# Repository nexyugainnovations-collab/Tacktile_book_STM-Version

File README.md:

# Tacktile Book STM (v1.0)

STM32-based hardware design for the Tacktile book, an interactive tactile book that plays audio in response to touch. This repository contains the PCB design files and the audio content used by the device.

Developed by **Nexyuga Innovations**.

## Contents

| Folder | Description |
|--------|-------------|
| pcb/ | Schematic and board layout source files |
| gerber/ | Fabrication outputs (Gerbers, drill files) |
| bom/ | Bill of materials |
| audio/ | Audio files used by the device |
| docs/ | Datasheets, notes and images |

Folder names may differ slightly from the actual layout. Update the table to match the repository.

## Hardware

- **Microcontroller:** STM32 (part number: TBD)
- **PCB design tool:** TBD
- **Audio:** stored audio played back through an amplifier and speaker
- **Input:** touch or button input from the tactile pages

## Getting Started

Clone the repository:

    git clone https://github.com/nexyugainnovations-collab/Tacktile_book_STM-Version.git
    cd Tacktile_book_STM-Version

1. Open the project file from the pcb/ folder in your PCB design tool.
2. To manufacture the board, send the contents of gerber/ to a PCB fabricator and use bom/ for component sourcing.
3. Flash the firmware to the STM32 using STM32CubeProgrammer or an ST-Link.

## Version History

| Version | Notes |
|---------|-------|
| v1.0 | Initial release: PCB and audio files |

## Contributors

- Pravin Balu ([*****](https://github.com/*****))
- Nithilan Saravanan ([@nithilan0710](https://github.com/nithilan0710))
- Nexyuga Innovations

## License

Proprietary. All rights reserved by Nexyuga Innovations.

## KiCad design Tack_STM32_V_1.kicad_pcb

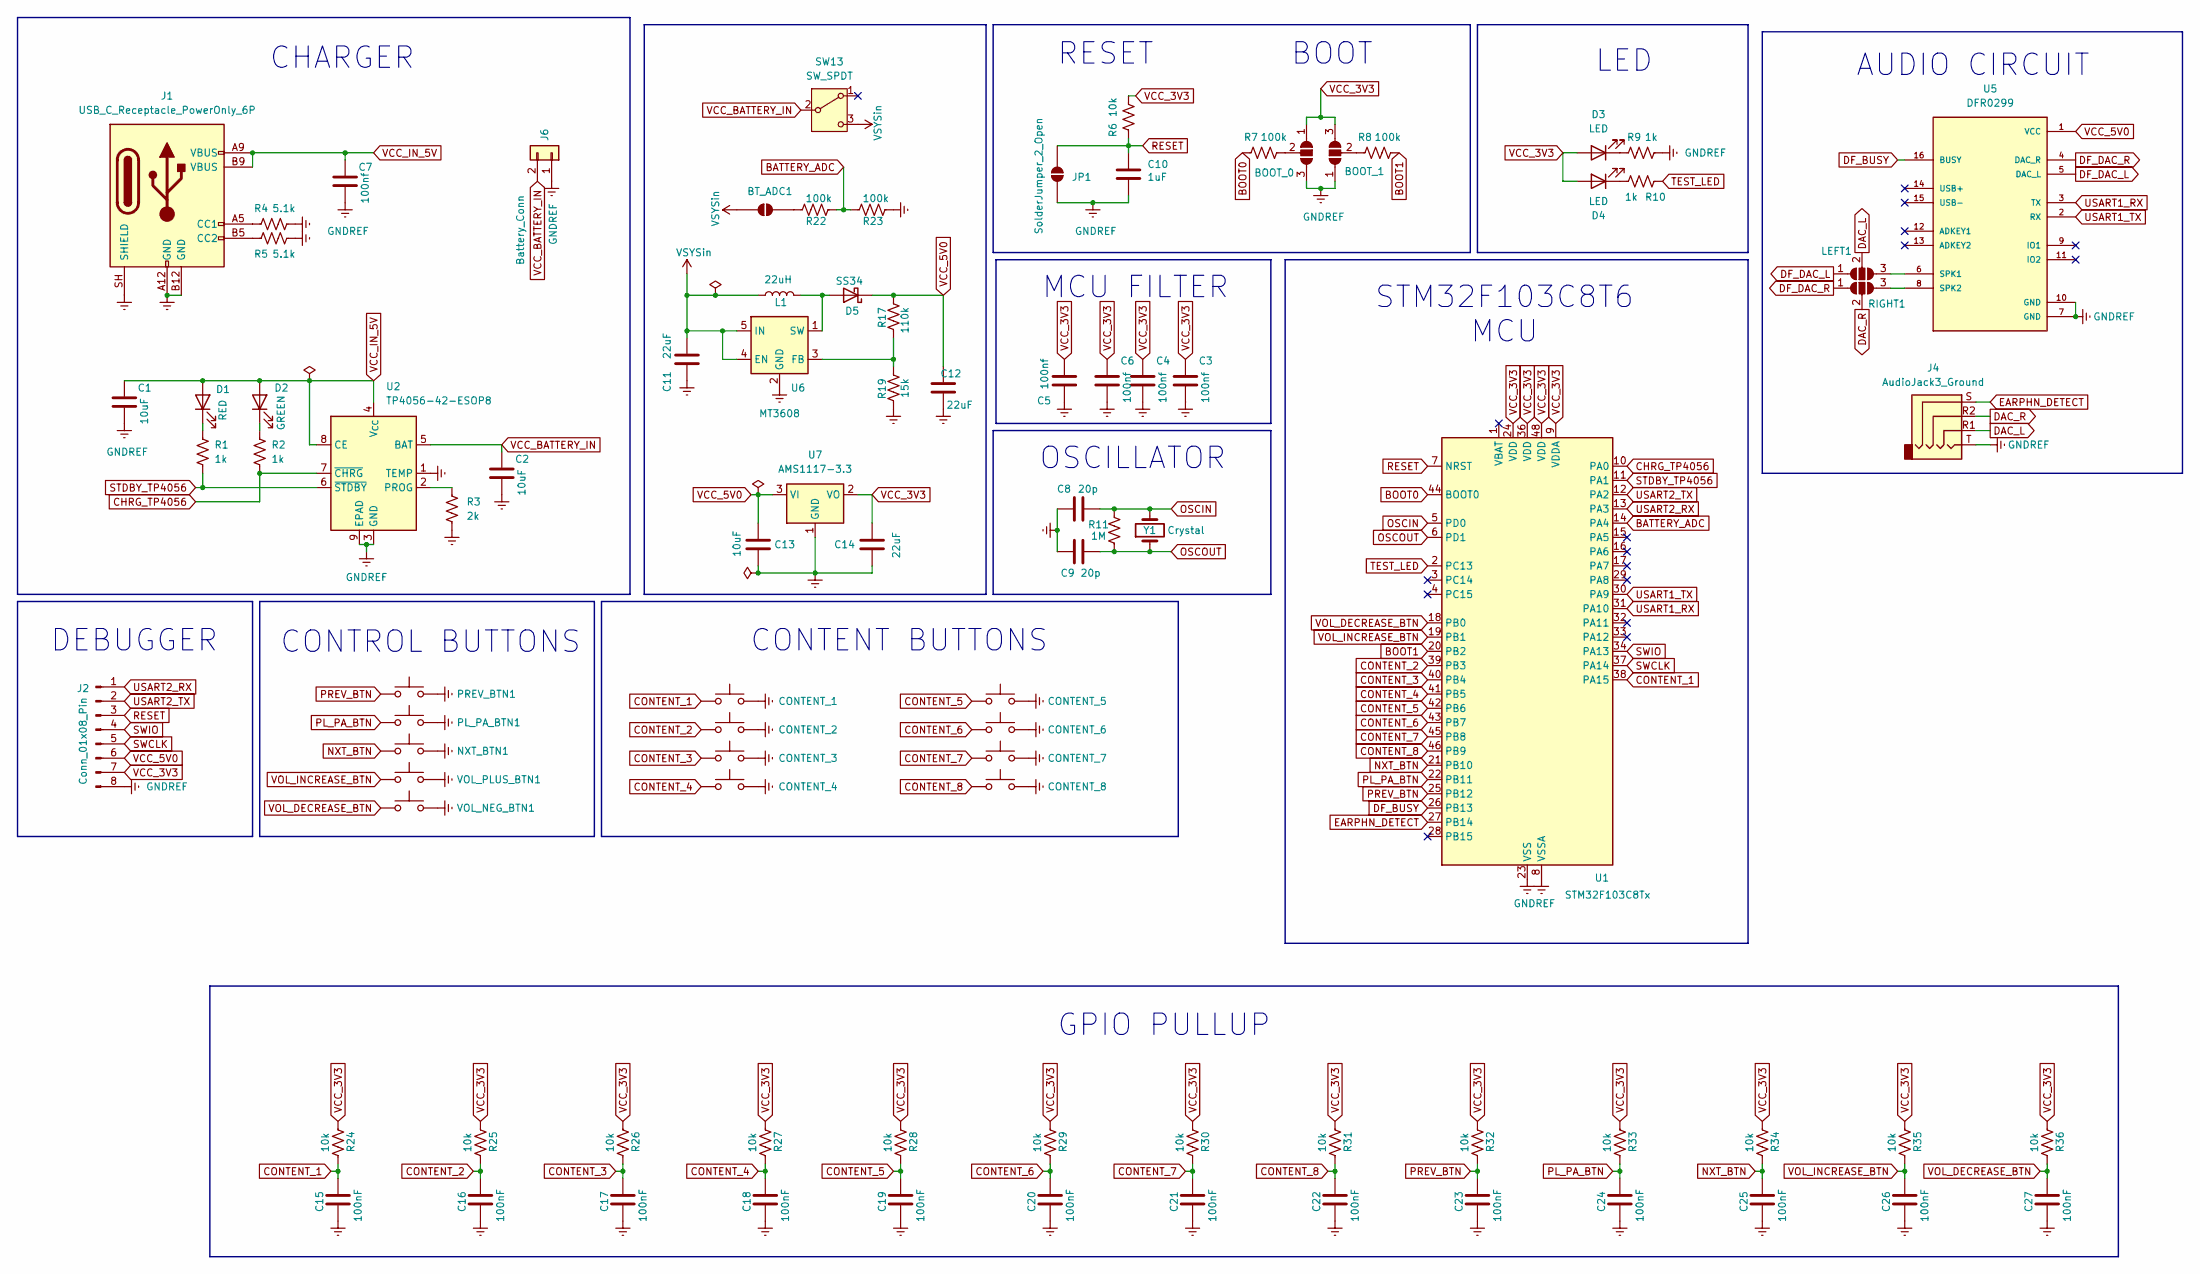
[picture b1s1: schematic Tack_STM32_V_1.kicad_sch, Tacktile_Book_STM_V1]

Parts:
BOOT_0, BOOT_1: SolderJumper_3_Open; SolderJumper-3_P1.3mm_Open_Pad1.0x1.5mm
BT_ADC1: SolderJumper_2_Open; SolderJumper-2_P1.3mm_Open_RoundedPad1.0x1.5mm
C1, C2, C13: 10uF; C_0603_1608Metric_Pad1.08x0.95mm_HandSolder
C3, C4, C5, C6, C7: 100nf; C_0603_1608Metric_Pad1.08x0.95mm_HandSolder
C8, C9: 20p; C_0603_1608Metric_Pad1.08x0.95mm_HandSolder
C10: 1uF; C_0603_1608Metric_Pad1.08x0.95mm_HandSolder
C11, C12, C14: 22uF; C_0603_1608Metric_Pad1.08x0.95mm_HandSolder
C15, C16, C17, C18, C19, C20, C21, C22, C23, C24, C25, C26, C27: 100nF; C_0603_1608Metric_Pad1.08x0.95mm_HandSolder
CONTENT_1: CONTENT_1; SW_CONTENT_2.5mm
CONTENT_2: CONTENT_2; SW_CONTENT_2.5mm
CONTENT_3: CONTENT_3; SW_CONTENT_2.5mm
CONTENT_4: CONTENT_4; SW_CONTENT_2.5mm
CONTENT_5: CONTENT_5; SW_CONTENT_2.5mm
CONTENT_6: CONTENT_6; SW_CONTENT_2.5mm
CONTENT_7: CONTENT_7; SW_CONTENT_2.5mm
CONTENT_8: CONTENT_8; SW_CONTENT_2.5mm
D1: RED; LED_0805_2012Metric_Pad1.15x1.40mm_HandSolder
D2: GREEN; LED_0805_2012Metric_Pad1.15x1.40mm_HandSolder
D3, D4: LED; LED_0805_2012Metric_Pad1.15x1.40mm_HandSolder
D5: SS34; D_SMB
J1: USB_C_Receptacle_PowerOnly_6P; USB_C_Receptacle_HRO_TYPE-C-31-M-17
J2: Conn_01x08_Pin; JST_PH_B8B-PH-K_1x08_P2.00mm_Vertical
J4: AudioJack3_Ground; Jack_3.5mm_PJ320D_Horizontal
J6: Battery_Conn; JST_EH_S2B-EH_1x02_P2.50mm_Horizontal
JP1: SolderJumper_2_Open; SolderJumper-2_P1.3mm_Open_RoundedPad1.0x1.5mm
L1: 22uH; L_Inductor 22uH – 5.2×5.8×4.5mm – CD54 – SMD
LEFT1: SolderJumper_3_Open; SolderJumper-3_P1.3mm_Open_Pad1.0x1.5mm
NXT_BTN1: NXT_BTN; SW_Tactile_SPST_Angled_PTS645Vx58-2LFS
PL_PA_BTN1: PL_PA_BTN; SW_Tactile_SPST_Angled_PTS645Vx58-2LFS
PREV_BTN1: SW_Tactile_SPST_Angled_PTS645Vx58-2LFS
R1, R2, R9, R10: 1k; R_0603_1608Metric_Pad0.98x0.95mm_HandSolder
R3: 2k; R_0603_1608Metric_Pad0.98x0.95mm_HandSolder
R4, R5: 5.1k; R_0603_1608Metric_Pad0.98x0.95mm_HandSolder
R6, R24, R25, R26, R27, R28, R29, R30, R31, R32, R33, R34, R35, R36: 10k; R_0402_1005Metric_Pad0.72x0.64mm_HandSolder
R7, R8, R22, R23: 100k; R_0603_1608Metric_Pad0.98x0.95mm_HandSolder
R11: 1M; R_0603_1608Metric_Pad0.98x0.95mm_HandSolder
R17: 110k; R_0603_1608Metric_Pad0.98x0.95mm_HandSolder
R19: 15k; R_0402_1005Metric_Pad0.72x0.64mm_HandSolder
RIGHT1: SolderJumper_3_Open; SolderJumper-3_P1.3mm_Open_Pad1.0x1.5mm
SW13: SW_SPDT; SS12F23G5 Mini SPDT Slide Switch Right Angle
U1: STM32F103C8Tx; LQFP-48_7x7mm_P0.5mm
U2: TP4056-42-ESOP8; SOIC-8-1EP_3.9x4.9mm_P1.27mm_EP2.41x3.3mm_ThermalVias
U5: DFR0299; MODULE_DFR0299
U6: MT3608; SOT-23-6
U7: AMS1117-3.3; SOT-223-3_TabPin2
VOL_NEG_BTN1: VOL_NEG_BTN; SW_Tactile_SPST_Angled_PTS645Vx58-2LFS
VOL_PLUS_BTN1: VOL_PLUS_BTN; SW_Tactile_SPST_Angled_PTS645Vx58-2LFS
Y1: Crystal; Crystal_SMD_HC49-SD

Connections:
BATTERY_ADC: R22.1, R23.2, U1.14 (PA4)
BOOT0: R7.1, U1.44 (BOOT0)
BOOT1: R8.2, U1.20 (PB2)
CHRG_TP4056: R2.2, U1.10 (PA0), U2.7 (~CHRG)
CONTENT_1: C15.1, CONTENT_1.1, R24.2, U1.38 (PA15)
CONTENT_2: C16.1, CONTENT_2.1, R25.2, U1.39 (PB3)
CONTENT_3: C17.1, CONTENT_3.1, R26.2, U1.40 (PB4)
CONTENT_4: C18.1, CONTENT_4.1, R27.2, U1.41 (PB5)
CONTENT_5: C19.1, CONTENT_5.1, R28.2, U1.42 (PB6)
CONTENT_6: C20.1, CONTENT_6.1, R29.2, U1.43 (PB7)
CONTENT_7: C21.1, CONTENT_7.1, R30.2, U1.45 (PB8)
CONTENT_8: C22.1, CONTENT_8.1, R31.2, U1.46 (PB9)
DAC_L: J4.R1, LEFT1.2 (C)
DAC_R: J4.R2, RIGHT1.2 (C)
DF_BUSY: U1.26 (PB13), U5.16 (BUSY)
DF_DAC_L: LEFT1.1 (A), U5.5 (DAC_L)
DF_DAC_R: RIGHT1.1 (A), U5.4 (DAC_R)
EARPHN_DETECT: J4.S, U1.27 (PB14)
GNDREF: BOOT_0.3 (B), BOOT_1.1 (A), C1.2, C2.2, C3.2, C4.2, C5.1, C6.2, C7.2, C8.1, C9.2, C10.2, C11.1, C12.1, C13.2, C14.2, C15.2, C16.2, C17.2, C18.2, C19.2, C20.2, C21.2, C22.2, C23.2, C24.2, C25.2, C26.2, C27.2, CONTENT_1.2, CONTENT_2.2, CONTENT_3.2, CONTENT_4.2, CONTENT_5.2, CONTENT_6.2, CONTENT_7.2, CONTENT_8.2, J1.A12 (GND), J1.B12 (GND), J1.SH (SHIELD), J2.8, J4.T, J6.1, JP1.1 (A), NXT_BTN1.2, PL_PA_BTN1.2, PREV_BTN1.2, R3.2, R4.2, R5.1, R9.2, R19.1, R23.1, U1.8 (VSSA), U1.23 (VSS), U1.35 (VSS), U1.47 (VSS), U2.1 (TEMP), U2.3 (GND), U2.9 (EPAD), U5.7 (GND), U5.10 (GND), U6.2 (GND), U7.1 (GND), VOL_NEG_BTN1.2, VOL_PLUS_BTN1.2
NXT_BTN: C25.1, NXT_BTN1.1, R34.2, U1.21 (PB10)
unnamed: BOOT_0.2 (C), R7.2
unnamed: BOOT_1.2 (C), R8.1
unnamed: BT_ADC1.1 (A), R22.2
unnamed: D1.1 (K), R1.1
unnamed: D2.1 (K), R2.1
unnamed: D3.1 (K), R9.1
unnamed: D4.1 (K), R10.2
unnamed: D5.2 (A), L1.2, U6.1 (SW)
unnamed: J1.A5 (CC1), R4.1
unnamed: J1.B5 (CC2), R5.2
unnamed: LEFT1.3 (B), U5.6 (SPK1)
unnamed: RIGHT1.3 (B), U5.8 (SPK2)
unnamed: R3.1, U2.2 (PROG)
unnamed: R17.1, R19.2, U6.3 (FB)
OSCIN: C8.2, R11.2, U1.5 (PD0), Y1.2
OSCOUT: C9.1, R11.1, U1.6 (PD1), Y1.1
PL_PA_BTN: C24.1, PL_PA_BTN1.1, R33.2, U1.22 (PB11)
PREV_BTN: C23.1, PREV_BTN1.1, R32.2, U1.25 (PB12)
RESET: C10.1, J2.3, JP1.2 (B), R6.1, U1.7 (NRST)
STDBY_TP4056: R1.2, U1.11 (PA1), U2.6 (~STDBY)
SWCLK: J2.5, U1.37 (PA14)
SWIO: J2.4, U1.34 (PA13)
TEST_LED: R10.1, U1.2 (PC13)
USART1_RX: U1.31 (PA10), U5.3 (TX)
USART1_TX: U1.30 (PA9), U5.2 (RX)
USART2_RX: J2.1, U1.13 (PA3)
USART2_TX: J2.2, U1.12 (PA2)
VCC_3V3: BOOT_0.1 (A), BOOT_1.3 (B), C3.1, C4.1, C5.2, C6.1, C14.1, D3.2 (A), D4.2 (A), J2.7, R6.2, R24.1, R25.1, R26.1, R27.1, R28.1, R29.1, R30.1, R31.1, R32.1, R33.1, R34.1, R35.1, R36.1, U1.9 (VDDA), U1.24 (VDD), U1.36 (VDD), U1.48 (VDD), U7.2 (VO)
VCC_5V0: C12.2, C13.1, D5.1 (K), J2.6, R17.2, U5.1 (VCC), U7.3 (VI)
VCC_BATTERY_IN: C2.1, J6.2, SW13.2 (B), U2.5 (BAT)
VCC_IN_5V: C1.1, C7.1, D1.2 (A), D2.2 (A), J1.A9 (VBUS), J1.B9 (VBUS), U2.4 (V_{CC}), U2.8 (CE)
VOL_DECREASE_BTN: C27.1, R36.2, U1.18 (PB0), VOL_NEG_BTN1.1
VOL_INCREASE_BTN: C26.1, R35.2, U1.19 (PB1), VOL_PLUS_BTN1.1
VSYSin: BT_ADC1.2 (B), C11.2, L1.1, SW13.3 (C), U6.4 (EN), U6.5 (IN)

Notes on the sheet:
CONTROL BUTTONS
CONTENT BUTTONS
RESET
OSCILLATOR
LED
CHARGER
BOOT
GPIO PULLUP
MCU FILTER
DEBUGGER
AUDIO CIRCUIT
STM32F103C8T6 MCU

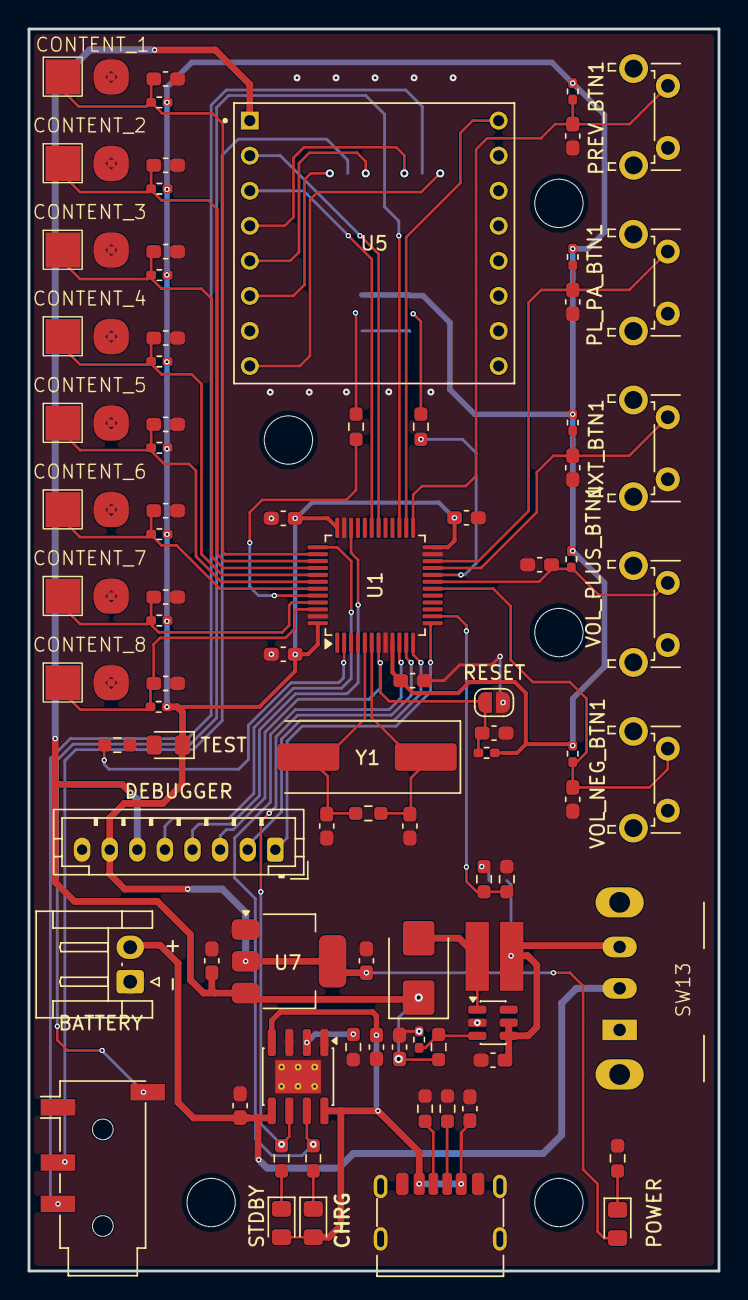
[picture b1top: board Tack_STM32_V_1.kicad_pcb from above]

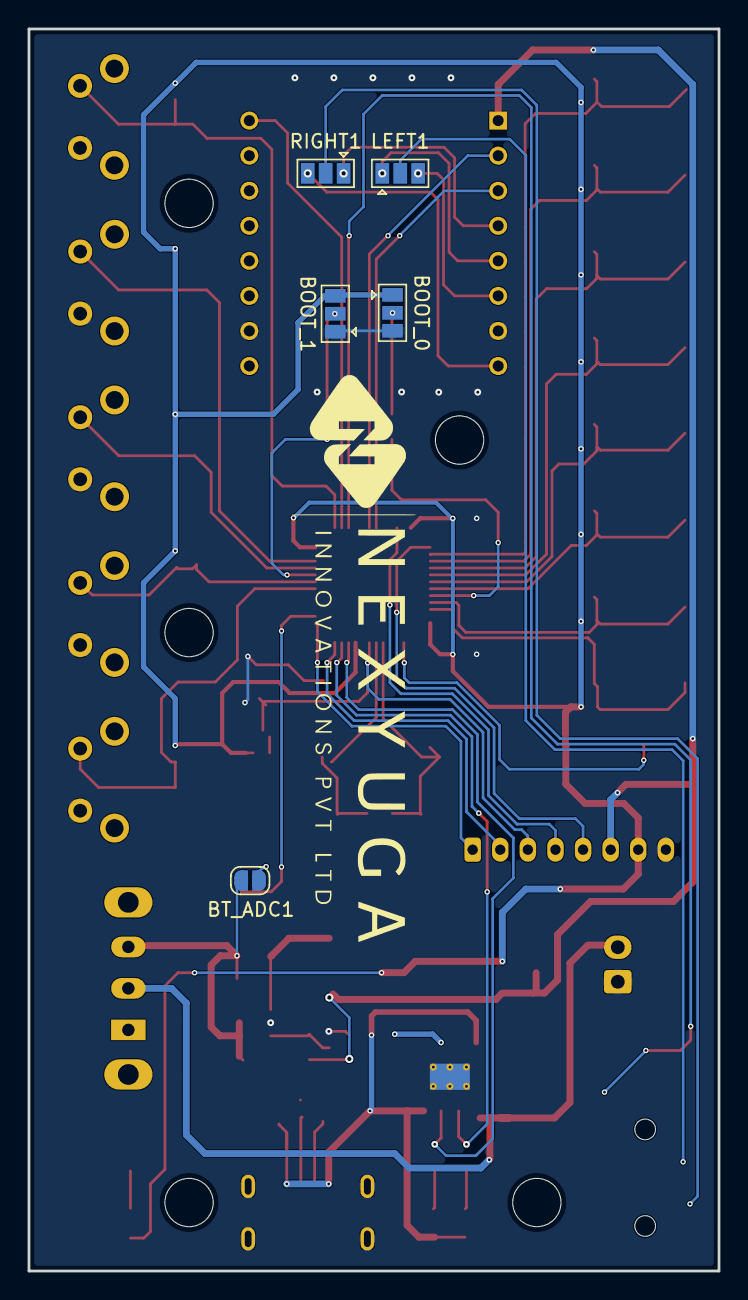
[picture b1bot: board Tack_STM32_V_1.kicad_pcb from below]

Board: 2 copper layers, 50.0 x 90.0 mm, 91 parts (5 on the bottom side), 54 nets.
